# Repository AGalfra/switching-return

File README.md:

# Conmutador de Retorno

## I. INTRODUCCIÓN
A pesar de la creciente demanda de servicios FTTH (Fiber To The Home), se puede decir que hoy en
día el despliegue de redes de HFC (Hybrid Fibre Coaxial) puede considerarse bastante masivo.
Para mantener los estándares de salud de red que la empresa exige y mejorar la experiencia del
cliente es que se trabaja exhaustivamente en tareas de mantenimiento preventivo.
El mayor problema de este tipo de redes es debido a la interferencia generada por las instalaciones
domiciliarias defectuosas y sobre todo a la alta tasa de conexiones clandestinas que son las mayores
generadoras de interferencias. Debido a esto es que aproximadamente el 90% de las intervenciones
en este tipo de redes es por los problemas antes mencionados. La cual es una tarea que demanda
demasiado tiempo y costo operativo.
Es por ello, que se propone el diseño de una herramienta que ayude a optimizar los tiempos de
trabajo y agilizar las tareas de búsqueda de interferencias.

## II. OBJETIVO
Diseño de un dispositivo que será utilizado como una herramienta adicional y complementaria a las
existentes para facilitar las tareas de mantenimiento en redes HFC, específicamente simplificar la
búsqueda de ruido y detección de interferencias en la banda de UPSTREAM en los nodos.

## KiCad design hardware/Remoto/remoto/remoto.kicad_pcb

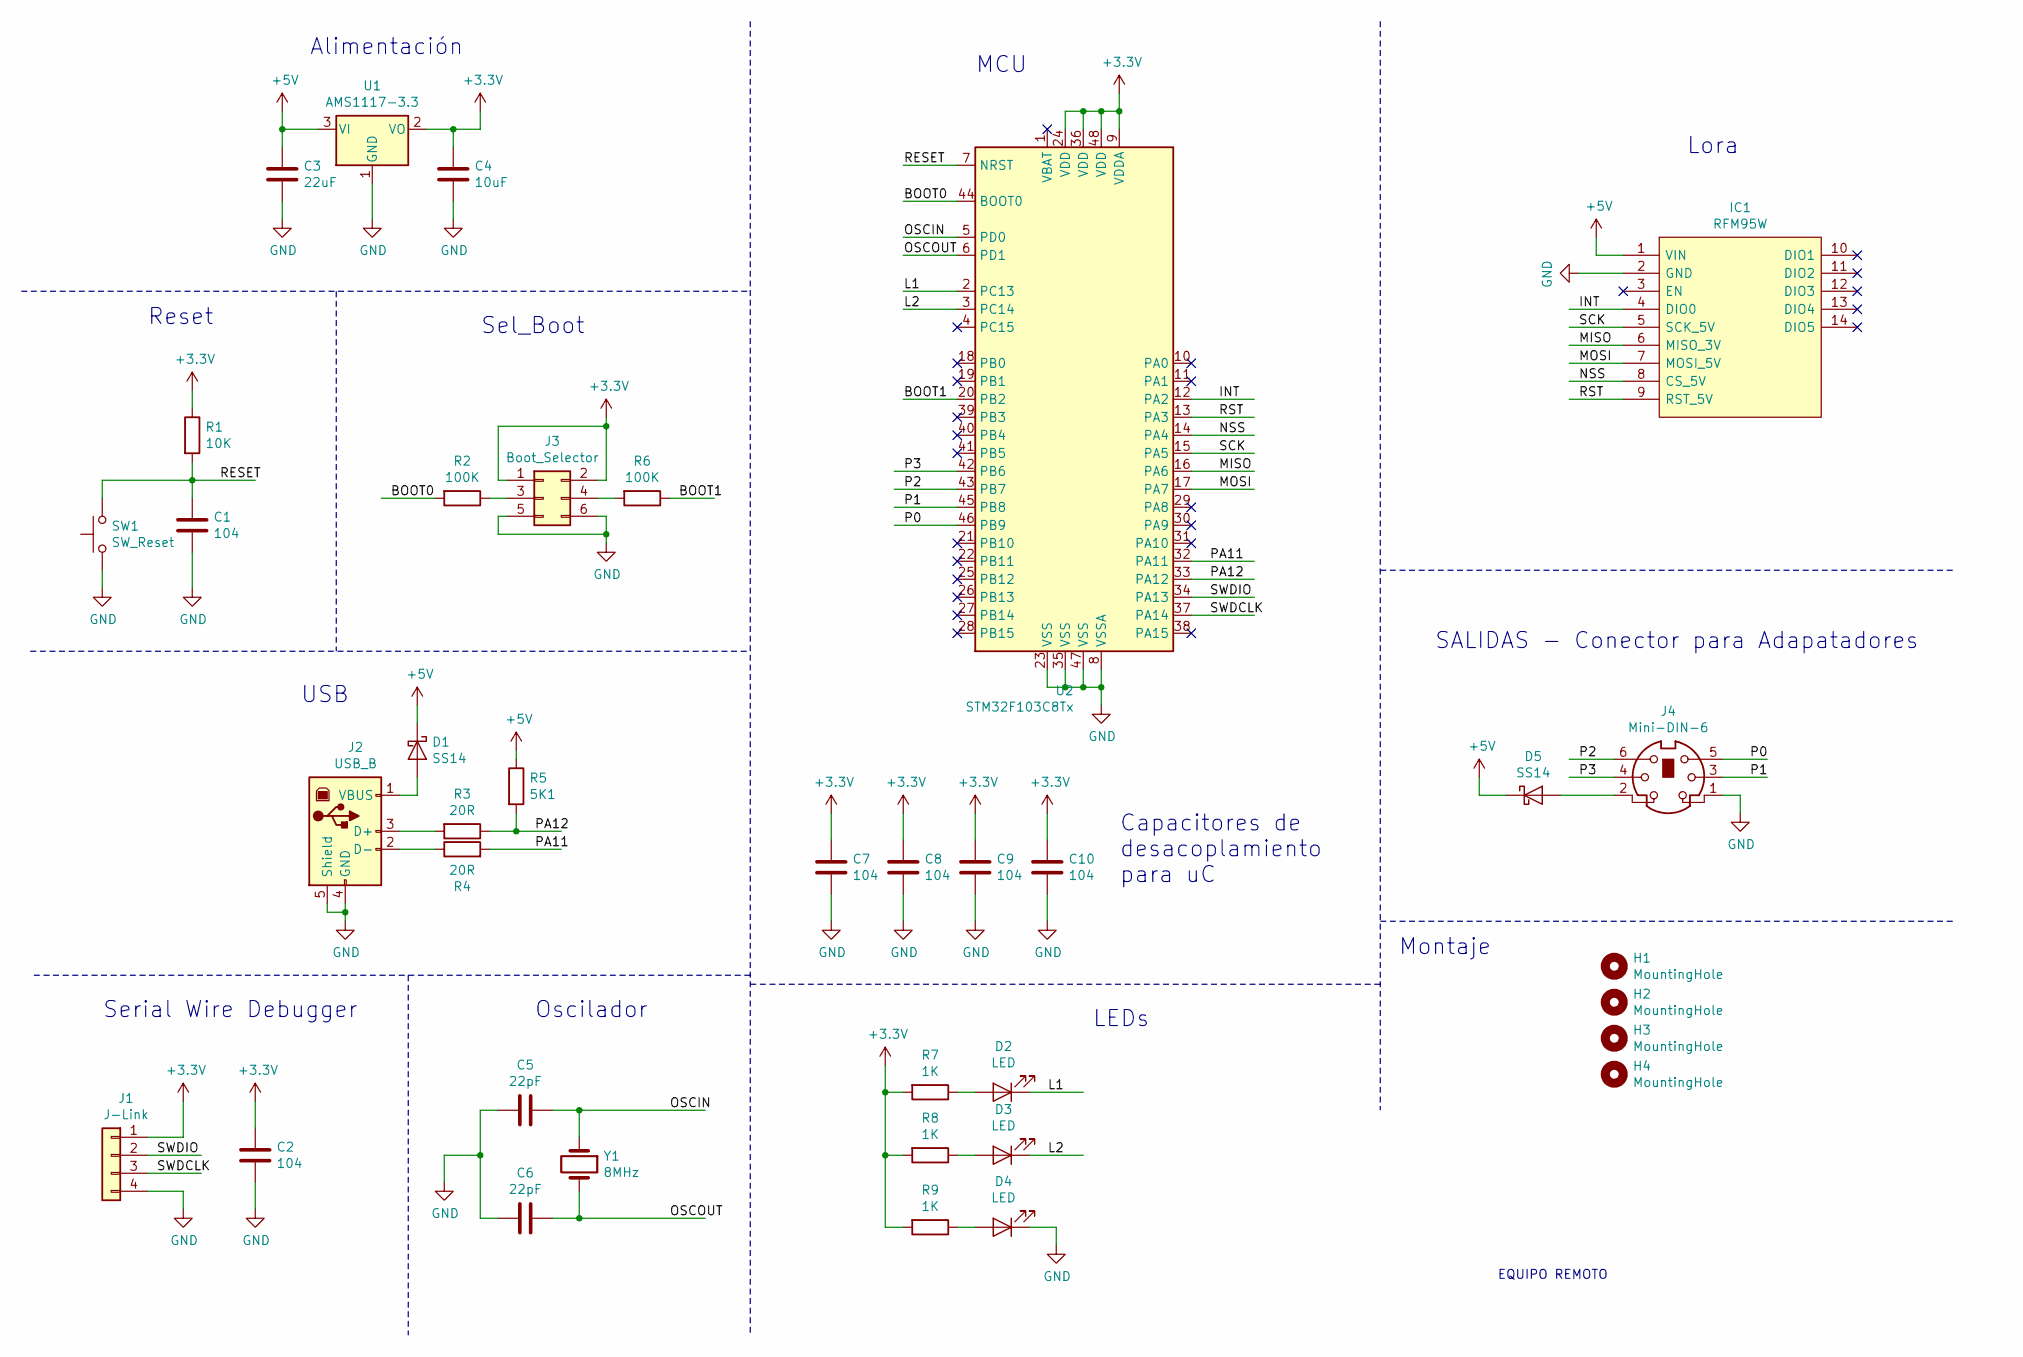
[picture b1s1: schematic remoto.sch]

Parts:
C1, C2, C7, C8, C9, C10: 104; C_0805_2012Metric
C3: 22uF; C_0805_2012Metric
C4: 10uF; C_0805_2012Metric
C5, C6: 22pF; C_0805_2012Metric
D1, D5: SS14; D_SMA
D2, D3: LED; LED_D3.0mm
D4: LED; LED_D3.0mm_Clear
H1, H2, H3, H4: MountingHole; MountingHole_3mm
IC1: RFM95W; Mouser Part Number 485-3072
J1: J-Link; PinHeader_1x04_P2.54mm_Vertical
J2: USB_B; conector_USB_tipoB
J3: Boot_Selector; PinHeader_2x03_P2.54mm_Vertical
J4: Mini-DIN-6; Mini-Din-6
R1: 10K; R_0805_2012Metric
R2, R6: 100K; R_0805_2012Metric
R3, R4: 20R; R_0805_2012Metric
R5: 5K1; R_0805_2012Metric
R7, R8, R9: 1K; R_0805_2012Metric
SW1: SW_Reset; SW_SPST_CK_RS282G05A3
U1: AMS1117-3.3; SOT-223-3_TabPin2
U2: STM32F103C8Tx; LQFP-48_7x7mm_P0.5mm
Y1: 8MHz; Crystal_HC18-U_Vertical

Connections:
+3V3: C2.1, C4.1, C7.1, C8.1, C9.1, C10.1, J1.1, J3.1, J3.2, R1.1, R7.2, R8.2, R9.2, U1.2 (VO), U2.9 (VDDA), U2.24 (VDD), U2.36 (VDD), U2.48 (VDD)
+5V: C3.1, D1.1 (K), D5.1 (K), IC1.1 (VIN), R5.1, U1.3 (VI)
/BOOT0: R2.2, U2.44 (BOOT0)
/BOOT1: R6.1, U2.20 (PB2)
/INT: IC1.4 (DIO0), U2.12 (PA2)
/L1: D2.1 (K), U2.2 (PC13)
/L2: D3.1 (K), U2.3 (PC14)
/MISO: IC1.6 (MISO_3V), U2.16 (PA6)
/MOSI: IC1.7 (MOSI_5V), U2.17 (PA7)
/NSS: IC1.8 (CS_5V), U2.14 (PA4)
/OSCIN: C5.1, U2.5 (PD0), Y1.1
/OSCOUT: C6.1, U2.6 (PD1), Y1.2
/P0: J4.5, U2.46 (PB9)
/P1: J4.3, U2.45 (PB8)
/P2: J4.6, U2.43 (PB7)
/P3: J4.4, U2.42 (PB6)
/PA11: R4.2, U2.32 (PA11)
/PA12: R3.1, R5.2, U2.33 (PA12)
/RESET: C1.1, R1.2, SW1.2, U2.7 (NRST)
/RST: IC1.9 (RST_5V), U2.13 (PA3)
/SCK: IC1.5 (SCK_5V), U2.15 (PA5)
/SWDCLK: J1.3, U2.37 (PA14)
/SWDIO: J1.2, U2.34 (PA13)
GND: C1.2, C2.2, C3.2, C4.2, C5.2, C6.2, C7.2, C8.2, C9.2, C10.2, D4.1 (K), IC1.2 (GND), J1.4, J2.4 (GND), J2.5 (Shield), J3.5, J3.6, J4.1, SW1.1, U1.1 (GND), U2.8 (VSSA), U2.23 (VSS), U2.35 (VSS), U2.47 (VSS)
unnamed: D1.2 (A), J2.1 (VBUS)
unnamed: D2.2 (A), R7.1
unnamed: D3.2 (A), R8.1
unnamed: D4.2 (A), R9.1
unnamed: D5.2 (A), J4.2
unnamed: J2.2 (D-), R4.1
unnamed: J2.3 (D+), R3.2
unnamed: J3.3, R2.1
unnamed: J3.4, R6.2

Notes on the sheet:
Serial Wire Debugger
Reset
USB
Alimentación
Sel_Boot
Oscilador
MCU
LEDs
Capacitores de desacoplamiento para uC
Montaje
SALIDAS - Conector para Adapatadores
EQUIPO REMOTO
Lora

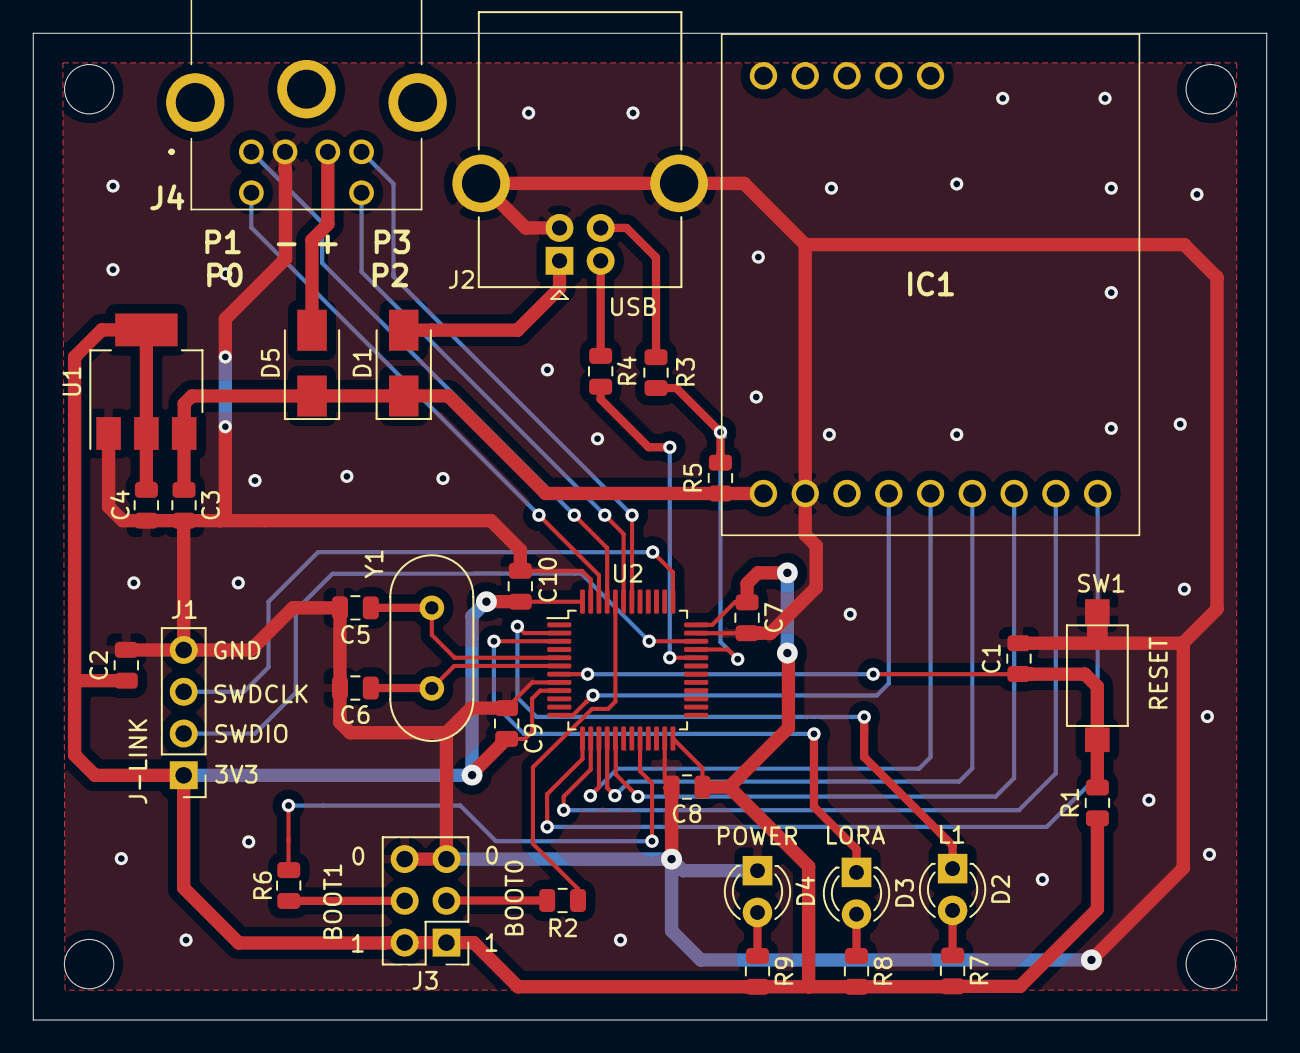
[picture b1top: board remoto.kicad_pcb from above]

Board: 2 copper layers, 75.0 x 60.0 mm, 37 parts (0 on the bottom side), 33 nets.

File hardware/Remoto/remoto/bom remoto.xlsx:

LISTA DE COMPONENTES - EQUIPO REMOTO
ref | value | footprint | part | Columna1
C1 | 104 | Capacitor_SMD:C_0805_2012Metric | C | 1.5
C10 | 104 | Capacitor_SMD:C_0805_2012Metric | C | 1.5
C2 | 104 | Capacitor_SMD:C_0805_2012Metric | C | 1.5
C3 | 22uF | Capacitor_SMD:C_0805_2012Metric | C | 1.5
C4 | 10uF | Capacitor_SMD:C_0805_2012Metric | C | 1.5
C5 | 22pF | Capacitor_SMD:C_0805_2012Metric | C | 1.5
C6 | 22pF | Capacitor_SMD:C_0805_2012Metric | C | 1.5
C7 | 104 | Capacitor_SMD:C_0805_2012Metric | C | 1.5
C8 | 104 | Capacitor_SMD:C_0805_2012Metric | C | 1.5
C9 | 104 | Capacitor_SMD:C_0805_2012Metric | C | 1.5
D1 | SS14 | Diode_SMD:D_SMA | D_Schottky | 2.2999999999999998
D2 | LED | LED_THT:LED_D3.0mm | LED | 1.26
D3 | LED | LED_THT:LED_D3.0mm | LED | 1.26
D4 | LED | LED_THT:LED_D3.0mm_Clear | LED | 1.26
D5 | SS14 | Diode_SMD:D_SMA | D_Schottky | 2.2999999999999998
IC1 | RFM95W | RFM95W:RFM95W | RFM95W | 2036
J1 | J-Link | PinHeader_1x04_P2.54mm_Vertical | Conn_01x04 | 30
J2 | USB_B | Modulos Varios:conector_USB_tipoB | USB_B | 76
J3 | Boot_Selector | PinHeader_2x03_P2.54mm_Vertical | Conn_02x03_Odd_Even | 0
J4 | Mini-DIN-6 | Modulos Varios:Mini-Din-6 | Mini-DIN-6 | 90
R1 | 10K | Resistor_SMD:R_0805_2012Metric | R | 1.25
R2 | 100K | Resistor_SMD:R_0805_2012Metric | R | 1.25
R3 | 20R | Resistor_SMD:R_0805_2012Metric | R | 1.25
R4 | 20R | Resistor_SMD:R_0805_2012Metric | R | 1.25
R5 | 5K1 | Resistor_SMD:R_0805_2012Metric | R | 1.25
R6 | 100K | Resistor_SMD:R_0805_2012Metric | R | 1.25
R7 | 1K | Resistor_SMD:R_0805_2012Metric | R | 1.25
R8 | 1K | Resistor_SMD:R_0805_2012Metric | R | 1.25
R9 | 1K | Resistor_SMD:R_0805_2012Metric | R | 1.25
SW1 | SW_Reset | Button_Switch_SMD:SW_SPST_CK_RS282G05A3 | SW_Push | 3
U1 | AMS1117-3.3 | Package_TO_SOT_SMD:SOT-223-3_TabPin2 | AMS1117-3.3 | 3.1
U2 | STM32F103C8Tx | Package_QFP:LQFP-48_7x7mm_P0.5mm | STM32F103C8Tx | 350
Y1 | 8MHz | Crystal:Crystal_HC18-U_Vertical | Crystal | 15
 |  | Antena |  | 1500
 |  | Conector SMA |  | 255
 |  | Gabinete |  | 800
 |  | Placa |  | 600
 |  |  |  | 5792.73

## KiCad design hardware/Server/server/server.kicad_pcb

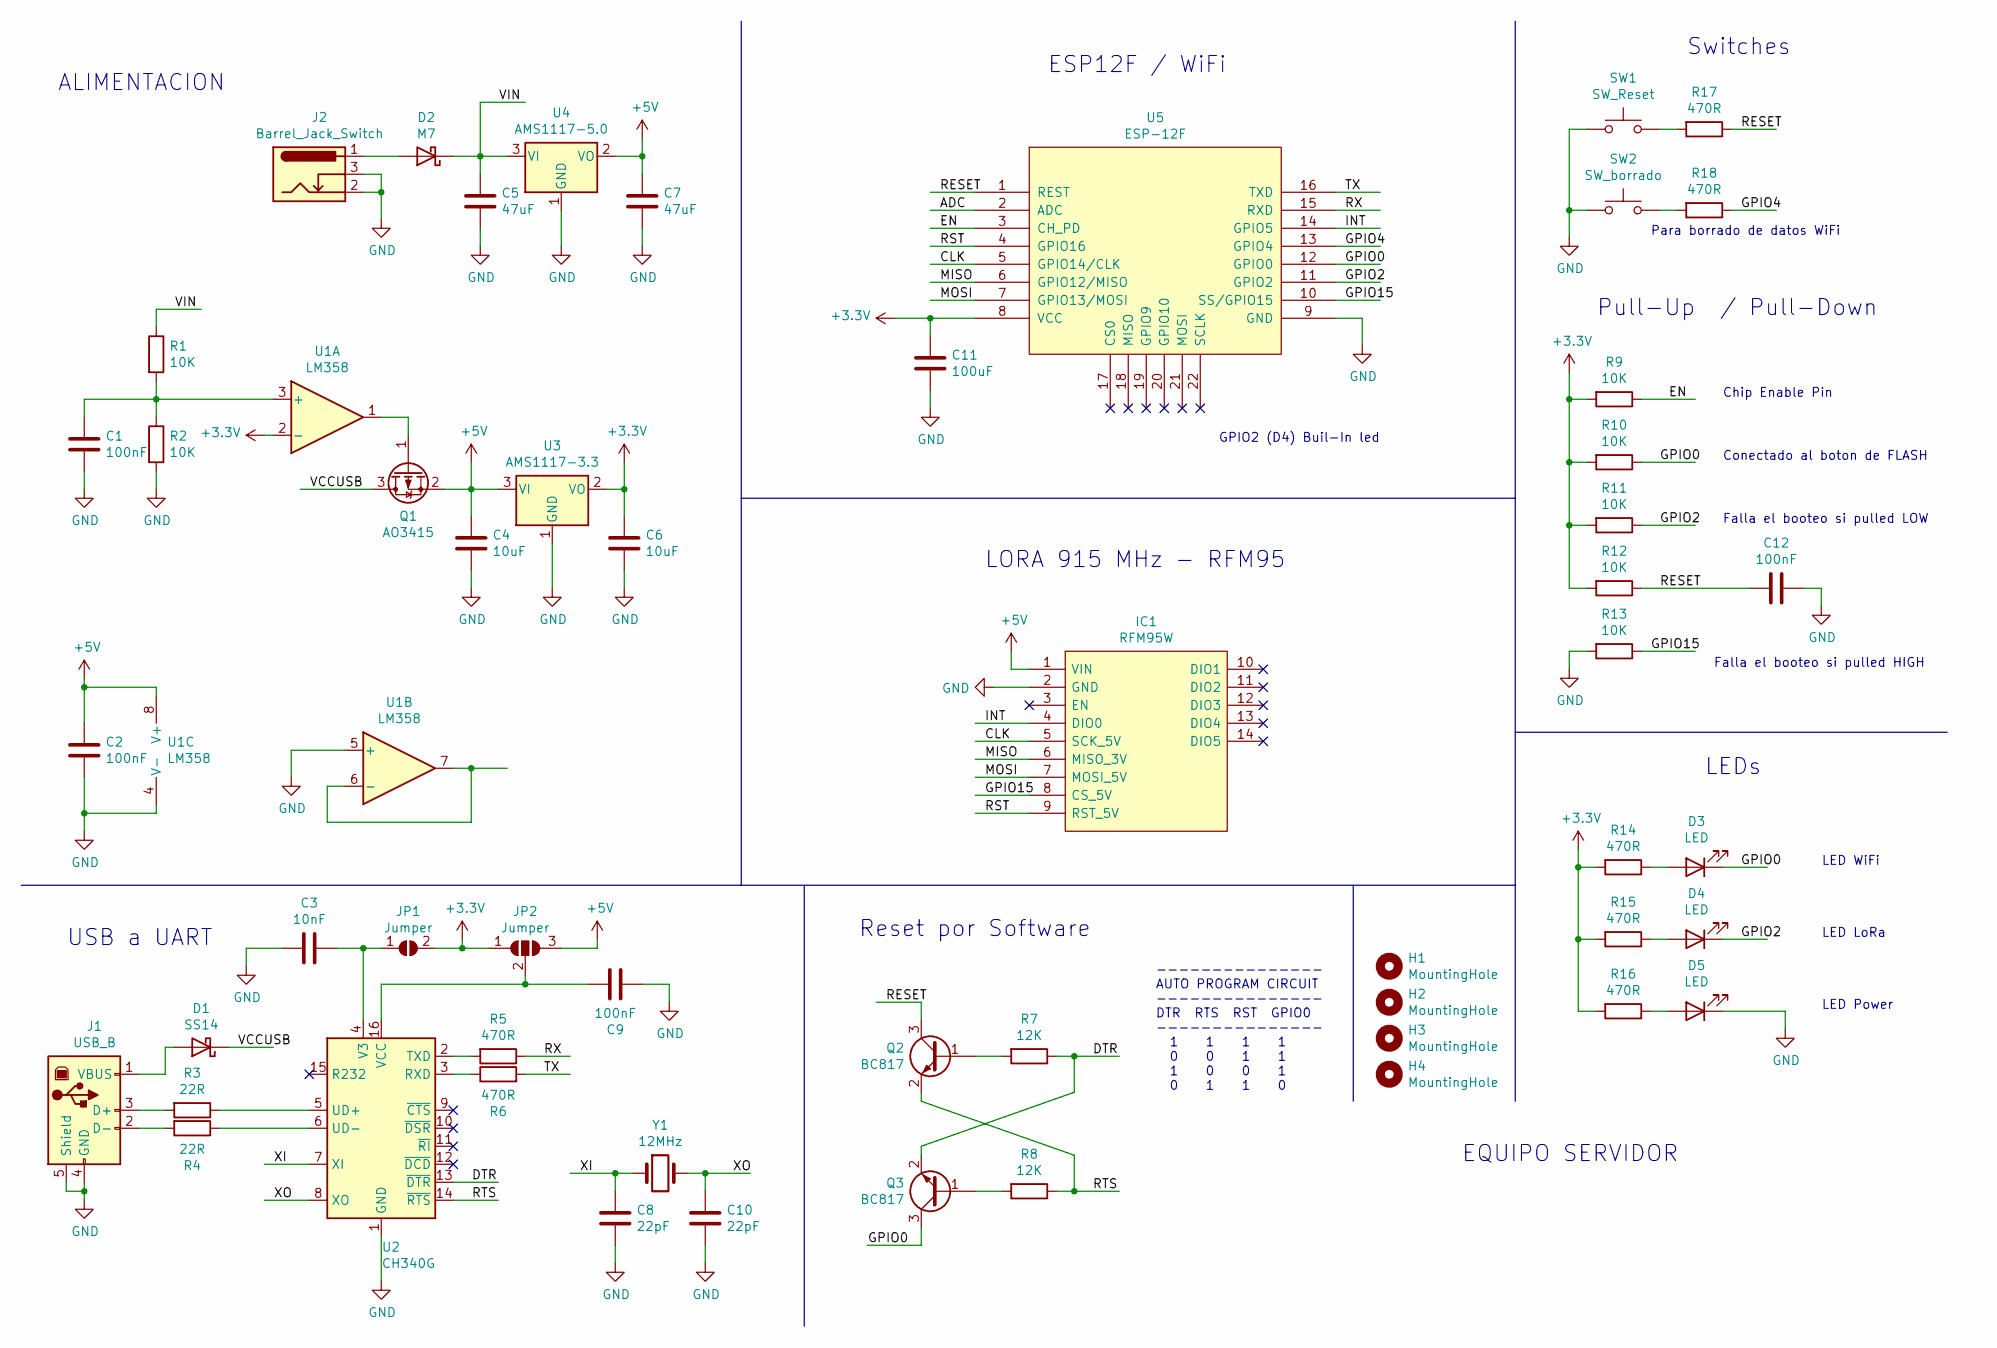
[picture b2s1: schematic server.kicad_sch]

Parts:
C1, C2, C9, C12: 100nF; C_0805_2012Metric
C3: 10nF; C_0805_2012Metric
C4, C6: 10uF; C_0805_2012Metric
C5, C7: 47uF; CP_Elec_8x10.5
C8, C10: 22pF; C_0805_2012Metric
C11: 100uF; CP_EIA-7343-31_Kemet-D
D1: SS14; D_SMA
D2: M7; D_SMA
D3, D4, D5: LED; LED_D3.0mm
H1, H2, H3, H4: MountingHole; MountingHole_3mm
IC1: RFM95W; Mouser Part Number 485-3072
J1: USB_B; conector_USB_tipoB
J2: Barrel_Jack_Switch; conector_jack_2.1mm
JP1: Jumper; SolderJumper-2_P1.3mm_Open_RoundedPad1.0x1.5mm
JP2: Jumper; SolderJumper-3_P1.3mm_Open_RoundedPad1.0x1.5mm
Q1: AO3415; SOT-23
Q2, Q3: BC817; SOT-23
R1, R2, R9, R10, R11, R12, R13: 10K; R_0805_2012Metric
R3, R4: 22R; R_0805_2012Metric
R5, R6, R14, R15, R16, R17, R18: 470R; R_0805_2012Metric
R7, R8: 12K; R_0805_2012Metric
SW1: SW_Reset; SW_SPST_CK_RS282G05A3
SW2: SW_borrado; SW_Tactile_SPST_Angled_PTS645Vx39-2LFS
U1: LM358; SOIC-8_3.9x4.9mm_P1.27mm
U2: CH340G; SOIC-16_3.9x9.9mm_P1.27mm
U3: AMS1117-3.3; SOT-223-3_TabPin2
U4: AMS1117-5.0; SOT-223-3_TabPin2
U5: ESP-12F; ESP-12E_SMD
Y1: 12MHz; cristal_SMD_ABLS7M2_7x4.1mm

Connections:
+3V3: C6.1, C11.1, JP1.2 (B), JP2.1 (A), R9.2, R10.2, R11.2, R12.2, R14.2, R15.2, R16.2, U1.2 (-), U3.2 (VO), U5.8 (VCC)
+5V: C2.1, C4.1, C7.1, IC1.1 (VIN), JP2.3 (B), Q1.2 (S), U1.8 (V+), U3.3 (VI), U4.2 (VO)
/ADC: U5.2 (ADC)
/CLK: IC1.5 (SCK_5V), U5.5 (GPIO14/CLK)
/DTR: Q3.2 (E), R7.1, U2.13 (~DTR)
/EN: R9.1, U5.3 (CH_PD)
/GPIO0: D3.1 (K), Q3.3 (C), R10.1, U5.12 (GPIO0)
/GPIO2: D4.1 (K), R11.1, U5.11 (GPIO2)
/GPIO4: R18.1, U5.13 (GPIO4)
/GPIO15: IC1.8 (CS_5V), R13.1, U5.10 (SS/GPIO15)
/INT: IC1.4 (DIO0), U5.14 (GPIO5)
/MISO: IC1.6 (MISO_3V), U5.6 (GPIO12/MISO)
/MOSI: IC1.7 (MOSI_5V), U5.7 (GPIO13/MOSI)
/RESET: C12.2, Q2.3 (C), R12.1, R17.1, U5.1 (REST)
/RST: IC1.9 (RST_5V), U5.4 (GPIO16)
/RTS: Q2.2 (E), R8.1, U2.14 (~RTS)
/RX: R5.1, U5.15 (RXD)
/TX: R6.2, U5.16 (TXD)
/VCCUSB: D1.1 (K), Q1.3 (D)
/VIN: C5.1, D2.1 (K), R1.1, U4.3 (VI)
/XI: C8.1, U2.7 (XI), Y1.1
/XO: C10.1, U2.8 (XO), Y1.2
GND: C1.2, C2.2, C3.2, C4.2, C5.2, C6.2, C7.2, C8.2, C9.2, C10.2, C11.2, C12.1, D5.1 (K), IC1.2 (GND), J1.4 (GND), J1.5 (Shield), J2.2, J2.3, R2.2, R13.2, SW1.1, SW2.1, U1.4 (V-), U1.5 (+), U2.1 (GND), U3.1 (GND), U4.1 (GND), U5.9 (GND)
unnamed: C1.1, R1.2, R2.1, U1.3 (+)
unnamed: C3.1, JP1.1 (A), U2.4 (V3)
unnamed: C9.1, JP2.2 (C), U2.16 (VCC)
unnamed: D1.2 (A), J1.1 (VBUS)
unnamed: D2.2 (A), J2.1
unnamed: D3.2 (A), R14.1
unnamed: D4.2 (A), R15.1
unnamed: D5.2 (A), R16.1
unnamed: J1.2 (D-), R4.2
unnamed: J1.3 (D+), R3.2
unnamed: Q1.1 (G), U1.1
unnamed: Q2.1 (B), R7.2
unnamed: Q3.1 (B), R8.2
unnamed: R3.1, U2.5 (UD+)
unnamed: R4.1, U2.6 (UD-)
unnamed: R5.2, U2.2 (TXD)
unnamed: R6.1, U2.3 (RXD)
unnamed: R17.2, SW1.2
unnamed: R18.2, SW2.2
unnamed: U1.6 (-), U1.7

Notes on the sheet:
LED Power
Pull-Up / Pull-Down
Chip Enable Pin
GPIO2 (D4) Buil-In led
LED WiFi
Conectado al boton de FLASH
Switches
Para borrado de datos WiFi
--------------- AUTO PROGRAM CIRCUIT --------------- DTR RTS RST GPIO0 --------------- 1 1 1 1 0 0 1 1 1 0 0 1 0 1 1 0
EQUIPO SERVIDOR
Reset por Software
LED LoRa
ALIMENTACION
LORA 915 MHz - RFM95
USB a UART
LEDs
Falla el booteo si pulled LOW
ESP12F / WiFi
Falla el booteo si pulled HIGH

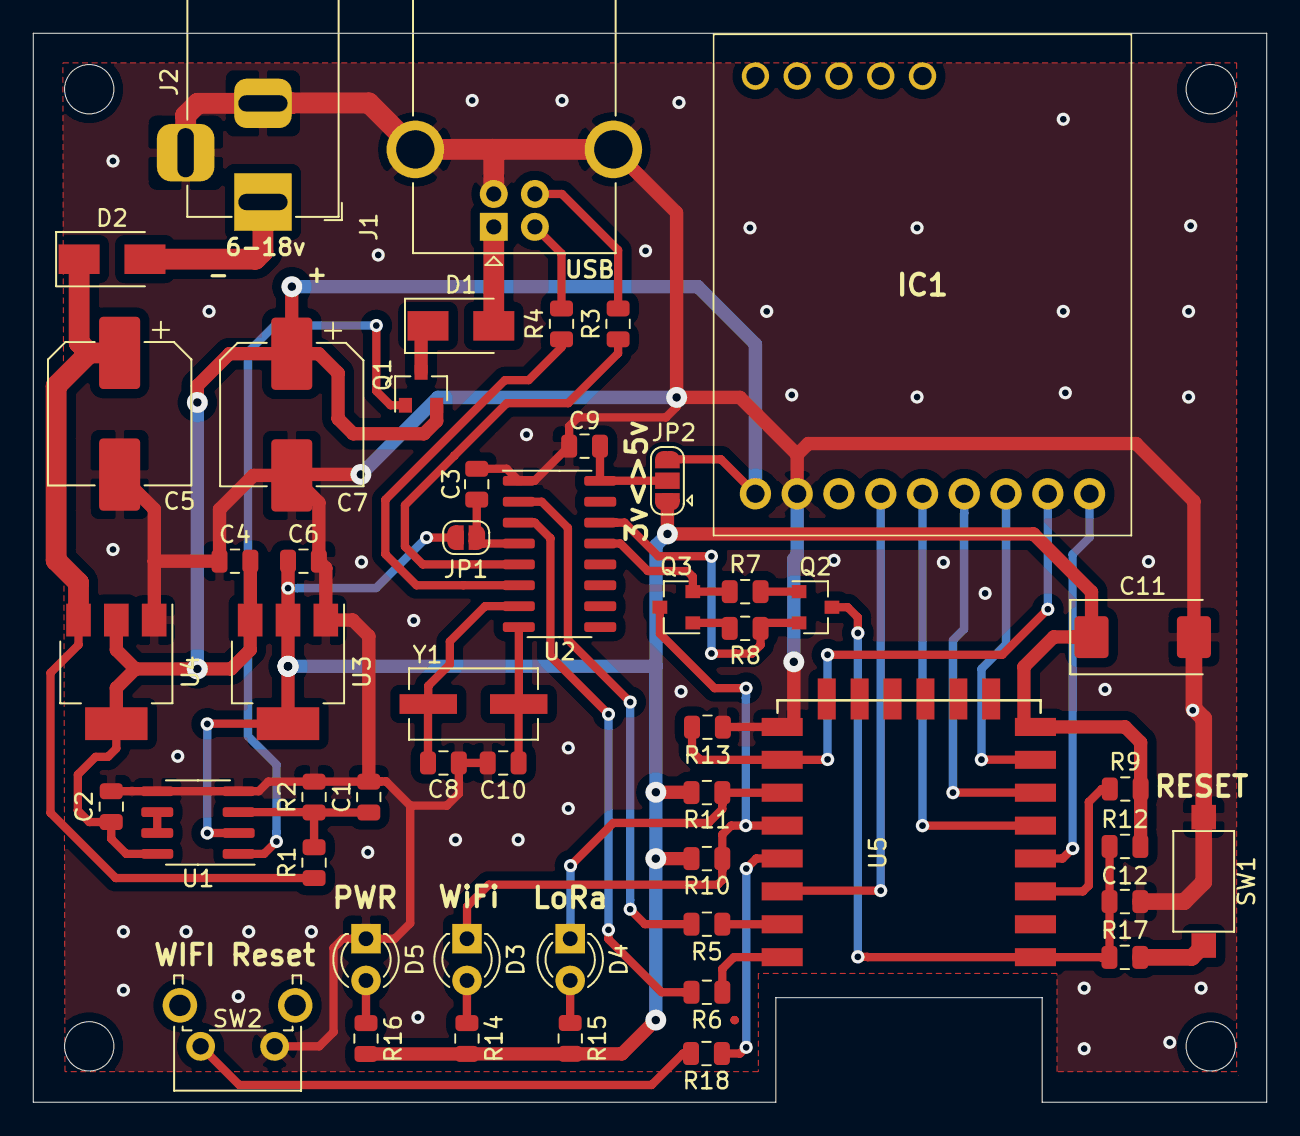
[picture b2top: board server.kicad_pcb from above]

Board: 2 copper layers, 75.0 x 65.0 mm, 55 parts (0 on the bottom side), 42 nets.

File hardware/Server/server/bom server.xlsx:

LISTA DE COMPONENTES - EQUIPO SERVIDOR
ref | value | footprint | part | Precio Unitario
C1 | 100nF | Capacitor_SMD:C_0805_2012Metric | C | 1.5
C10 | 22pF | Capacitor_SMD:C_0805_2012Metric | C | 1.5
C11 | 100uF | Capacitor_Tantalum_SMD:CP_EIA-7343-31_Kemet-D | C | 22
C12 | 100nF | Capacitor_SMD:C_0805_2012Metric | C | 1.5
C2 | 100nF | Capacitor_SMD:C_0805_2012Metric | C | 1.5
C3 | 10nF | Capacitor_SMD:C_0805_2012Metric | C | 1.5
C4 | 10uF | Capacitor_SMD:C_0805_2012Metric | C | 1.5
C5 | 47uF | Capacitor_SMD:CP_Elec_8x10.5 | C | 10.3
C6 | 10uF | Capacitor_SMD:C_0805_2012Metric | C | 1.5
C7 | 47uF | Capacitor_SMD:CP_Elec_8x10.5 | C | 10.3
C8 | 22pF | Capacitor_SMD:C_0805_2012Metric | C | 1.5
C9 | 100nF | Capacitor_SMD:C_0805_2012Metric | C | 1.5
D1 | SS14 | Diode_SMD:D_SMA | D_Schottky | 2.2999999999999998
D2 | M7 | Diode_SMD:D_SMA | B120-E3 | 1.5
D3 | LED | LED_THT:LED_D3.0mm | LED | 1.26
D4 | LED | LED_THT:LED_D3.0mm | LED | 1.26
D5 | LED | LED_THT:LED_D3.0mm | LED | 1.26
IC1 | RFM95W | RFM95W:RFM95W | RFM95W | 2036
J1 | USB_B | Modulos Varios:conector_USB_tipoB | USB_B | 76
J2 | Jack_Switch | Modulos Varios:conector_jack_2.1mm | Barrel_Jack_Switch | 11
Q1 | AO3415 | Package_TO_SOT_SMD:SOT-23 | AO3401A | 4
Q2 | BC817 | Package_TO_SOT_SMD:SOT-23 | BC817 | 2.2000000000000002
Q3 | BC817 | Package_TO_SOT_SMD:SOT-23 | BC817 | 2.2000000000000002
R1 | 10K | Resistor_SMD:R_0805_2012Metric | R | 1.25
R10 | 10K | Resistor_SMD:R_0805_2012Metric | R | 1.25
R11 | 10K | Resistor_SMD:R_0805_2012Metric | R | 1.25
R12 | 10K | Resistor_SMD:R_0805_2012Metric | R | 1.25
R13 | 10K | Resistor_SMD:R_0805_2012Metric | R | 1.25
R14 | 470R | Resistor_SMD:R_0805_2012Metric | R | 1.25
R15 | 470R | Resistor_SMD:R_0805_2012Metric | R | 1.25
R16 | 470R | Resistor_SMD:R_0805_2012Metric | R | 1.25
R17 | 470R | Resistor_SMD:R_0805_2012Metric | R | 1.25
R18 | 470R | Resistor_SMD:R_0805_2012Metric | R | 1.25
R2 | 10K | Resistor_SMD:R_0805_2012Metric | R | 1.25
R3 | 22R | Resistor_SMD:R_0805_2012Metric | R | 1.25
R4 | 22R | Resistor_SMD:R_0805_2012Metric | R | 1.25
R5 | 470R | Resistor_SMD:R_0805_2012Metric | R | 1.25
R6 | 470R | Resistor_SMD:R_0805_2012Metric | R | 1.25
R7 | 12K | Resistor_SMD:R_0805_2012Metric | R | 1.25
R8 | 12K | Resistor_SMD:R_0805_2012Metric | R | 1.25
R9 | 10K | Resistor_SMD:R_0805_2012Metric | R | 1.25
SW1 | SW_Reset | Button_Switch_SMD | SW_Push | 3
SW2 | SW_borrado | Button_Switch_THT_Angled | SW_Push | 3.5
U1 | LM358 | Package_SO:SOIC-8_3.9x4.9mm_P1.27mm | LM358 | 7
U2 | CH340G | Package_SO:SOIC-16_3.9x9.9mm_P1.27mm | CH340G | 80
U3 | AMS1117-3.3 | Package_TO_SOT_SMD:SOT-223-3_TabPin2 | AMS1117-3.3 | 3.1
U4 | AMS1117-5.0 | Package_TO_SOT_SMD:SOT-223-3_TabPin2 | AMS1117-5.0 | 3.1
U5 | ESP-12F | ESP8266:ESP-12E_SMD | ESP-12F | 200
Y1 | 12MHz | Modulos Varios:cristal_SMD_ABLS7M2_7x4.1mm | Crystal | 15
 |  | Antena |  | 1500
 |  | Conector SMA |  | 255
 |  | Gabinete |  | 800
 |  | Placa |  | 600
 |  |  |  | 5687.2799999999988

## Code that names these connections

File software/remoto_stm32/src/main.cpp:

//------------------------------------------------------------------------
//                                LIBRERIAS
//------------------------------------------------------------------------
#include <Arduino.h>

#include <RHReliableDatagram.h>
#include <RH_RF95.h>
#include <SPI.h>
//------------------------------------------------------------------------
//                                CONSTANTES
//------------------------------------------------------------------------
#define SERVER_ADDRESS  1         // Direccion del equipo Servidor
#define REMOTE_ADDRESS  2         // Direccion del equipo Remoto

#define BOOT1           PB2       // para condicion de arranque 

#define RFM95_CS        PA4       // Pin de CS del modulo SPI
#define RFM95_RST       PA3       // Pin de reset modulo Lora
#define RFM95_INT       PA2       // Pin de interrupcion para Rx Lora
#define LED_LORA        PC14      // Pin par indicar actividad de Tx/Rx
//#define LED_LORA        PC13    // Pin par indicar actividad de Tx/Rx
#define POWER_LORA      20        // Potencia de transmision (de 5 a 23)
#define RETRIES_LORA    3         // Cantidad de reintentos (de 3 a 6)
#define TIMEOUT_LORA    4         // Timeout entre reintentos (4 a 8)
#define RF95_FREQ       915.0     // Frecuencia del tranceptor Lora
#define CTE_TO_NORMAL   50        // CTE para ajustar el timeout
#define CTE_TO_SLOW     500      // CTE para ajustar el timeout en slow
#define TIEMPO          80000     // 80 segundos timeout para millis()
                                  // Definicion de pines de salida
#define PORT0           PB9       // para P1
#define PORT1           PB8       // para P2/P3
#define PORT2           PB7       // para P4
#define PORT3           PB6       // para P5/P6

#define LOGICA_NEGATIVA 1         // Logica neg para control de puertos
//------------------------------------------------------------------------
//                                 VARIABLES
//------------------------------------------------------------------------
char ver_soft[]   = "\nConmutador de Retorno v1.0";
char bienvenida[] = "----- Equipo Remoto -----\n";
char buf[RH_RF95_MAX_MESSAGE_LEN];

uint8_t  idport;                      //Id de puerto
bool     estado;                      //Estado del puerto variable aux
bool     gpio[4] = {0,0,0,0};         //Matriz de estado de los puertos
uint8_t  ports[4] = {PORT0, PORT1,    
                     PORT2, PORT3};   //Matriz de puertos
char     packet[14] = "updateGPIO.";  //Array de datos Lora 
uint8_t  i;                           //Contador
bool     rebooting = 1;               //Indica que el uC esta iniciando
bool     slow = false;                //Flag de modulación lenta
bool     refresh = false;
uint8_t  power = POWER_LORA;          //Potencia de tx LoRa 
uint8_t  retries = RETRIES_LORA;      //Cant. de reintentos p/ sendtoWait
uint16_t timeout = TIMEOUT_LORA;      //Timeout entre reintentos
uint16_t aux;
uint32_t previousMillis;
//------------------------------------------------------------------------
//                          FUNCIONES - CODIGO ANEXO
//------------------------------------------------------------------------
#include "RF95_Utils.hpp"      //Funciones para el manejo del modulo RFM95

//------------------------------------------------------------------------
//Imprime en consola de los datos recibidos por el modulo Lora junto con 
//los niveles de recepcion.
void printRcv(char *buf, uint8_t from_adr) {
  Serial.println(""); 
  Serial.print("De: 0x");
  Serial.print(from_adr, HEX);
  Serial.print("-> ");
  Serial.println((char*)buf);
  //RH_RF95::printBuffer("Trama completa: ", buf, len);
  Serial.print("RSSI: ");
  Serial.print(rf95.lastRssi(), DEC);
  Serial.print(", SNR: ");
  Serial.println(rf95.lastSNR(), DEC);  
}

//------------------------------------------------------------------------
//Envia estado actualizado de todos los puertos y los imprime en consola.
void updateGPIO(void) {                   
  for (i=0;i<4;i++) {    
    if(LOGICA_NEGATIVA)
      gpio[i] = !(digitalRead(ports[i]));   
    else
      gpio[i] = digitalRead(ports[i]);   

    itoa(i, packet+11, 10);
    itoa(gpio[i], packet+12, 10);
    packet[13] = 0;
    Serial.println(packet); 
    delay(10);
    send_lora();
    Serial.println("");     
  }  
}

//------------------------------------------------------------------------
//                                SETUP
//------------------------------------------------------------------------
void setup() {

  pinMode(BOOT1, INPUT); 
  pinMode(LED_LORA, OUTPUT);            //configuracion de pines
  digitalWrite(LED_LORA, HIGH);         
  pinMode(RFM95_RST, OUTPUT);
  digitalWrite(RFM95_RST, HIGH);
  
  if(digitalRead(BOOT1) == 1)
    while (!Serial);              //espera hasta que la consola este lista
  
  Serial.begin(115200);
  delay(1000);  
  Serial.println(ver_soft);  
  delay(10);
  Serial.println(bienvenida);

  for (i=0;i<4;i++) {           //Configuracion e inicializacion de pines
    pinMode(ports[i], OUTPUT);   
    if(LOGICA_NEGATIVA)       
      digitalWrite(ports[i], 0);    
    else
      digitalWrite(ports[i], 1);
  }  
  Serial.println("ON todos los puertos");
  
  InitRF95();                           //inicializacion del modulo RFM95
  delay(50);
}

//------------------------------------------------------------------------
//                                BUCLE PRINCIPAL
//------------------------------------------------------------------------
void loop() {

  if(rebooting){
    updateGPIO();         //Al reiniciar enviar estado de todos los puertos
    rebooting = 0;
  }
  if(((millis() - previousMillis) >= TIEMPO) && (slow == 1)) {
    if(refresh == 0) {              //si no se recibio el refresh <>...
      slow = 0;
      setModulation();            //volver a modulacion normal(por defecto)
    }
    refresh = 0;
    previousMillis = millis();
  }

  //-----------------------------  
  if (manager.available()) {      //Verificar si hay un mje LoRa disponible
    uint8_t len = sizeof(buf);
    uint8_t from, indice; 
    String rx;

    //recibo la trama y envio el acuse de recibo automaticamente
    if (manager.recvfromAck((uint8_t *)buf, &len, &from)) {   

      digitalWrite(LED_LORA, LOW);
      delay(50);                  
      printRcv(buf, from);               //imprimir en consola datos de rx
      digitalWrite(LED_LORA, HIGH);
            
      rx = String(buf);
      //----------------------------- Comando setGPIO
      if (rx.indexOf("setGPIO.") != -1) { 
        indice = rx.indexOf("setGPIO.");
        idport = rx.substring(indice+8, indice+9).toInt();
        estado = rx.substring(indice+9, indice+10).toInt();
        
        if(LOGICA_NEGATIVA)
          digitalWrite(ports[idport], (!estado)); 
        else
          digitalWrite(ports[idport], (estado));
      }      
      //----------------------------- Comando getGPIO
      else if (rx.indexOf("getGPIO") != -1) {
        Serial.println("");
        delay(50);    
        updateGPIO();            //envio updateGPIO de todos los puertos
      }
      //----------------------------- Comando txpower
      else if (rx.indexOf("txpower.") != -1) { 
        indice = rx.indexOf("txpower.");
        if(rx.substring(indice+9, indice+10) == 0)
          power = rx.substring(indice+8, indice+9).toInt();
        else {
          power = 10 * rx.substring(indice+8, indice+9).toInt();
          power += rx.substring(indice+9, indice+10).toInt();
        }
        rf95.setTxPower(power, false);
        Serial.print("setTxPower-> ");
        Serial.println(power, DEC);        
      }
      //----------------------------- Comando retries
      else if (rx.indexOf("retries.") != -1) { 
        indice = rx.indexOf("retries.");
        retries = rx.substring(indice+8, indice+9).toInt();   
        manager.setRetries(retries);
        Serial.print("setRetries-> ");
        Serial.println(retries, DEC);        
      }
      //----------------------------- Comando timeout
      else if (rx.indexOf("timeout.") != -1) {  
        indice = rx.indexOf("timeout.");
        timeout = rx.substring(indice+8, indice+9).toInt();           
        
        if(slow)
          aux = timeout * CTE_TO_SLOW;
        else
          aux = timeout * CTE_TO_NORMAL;
        manager.setTimeout(aux);   
        Serial.print("setTimeout-> ");
        Serial.println(aux, DEC);        
      }
      //----------------------------- Comando setMOD
      else if (rx.indexOf("setMOD.") != -1) {
        indice = rx.indexOf("setMOD.");
        slow = rx.substring(indice+7, indice+8).toInt();      
        setModulation();
        previousMillis = millis();
      }
      //----------------------------- Comando refresh
      else if (rx.indexOf("<>") != -1) {
        refresh = 1;        
      }
    }
  } 
}

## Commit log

2023-05-11 Update README.md
    edit readme
2023-05-11 upload files
2023-05-11 edit renders
2023-05-11 edit2
